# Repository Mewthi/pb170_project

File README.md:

LED - LA,LB,LC,LD,LE
Vstupy generovane citacom - (0-3)

    I       Q0    Q1    Q2    Q3    Q4
    00 -> ( 16 ->  8 ->  4 ->  2 ->  1)  
    01 -> ( 16 ->  1 ->  8 ->  2 ->  4) 
    10 -> ( 17 -> 10 ->  4 -> 20 -> 21)  
    11 -> (  4 -> 10 -> 17 -> 10 ->  4)  
  
Podrobna dokumentacia v /tex/main.pdf

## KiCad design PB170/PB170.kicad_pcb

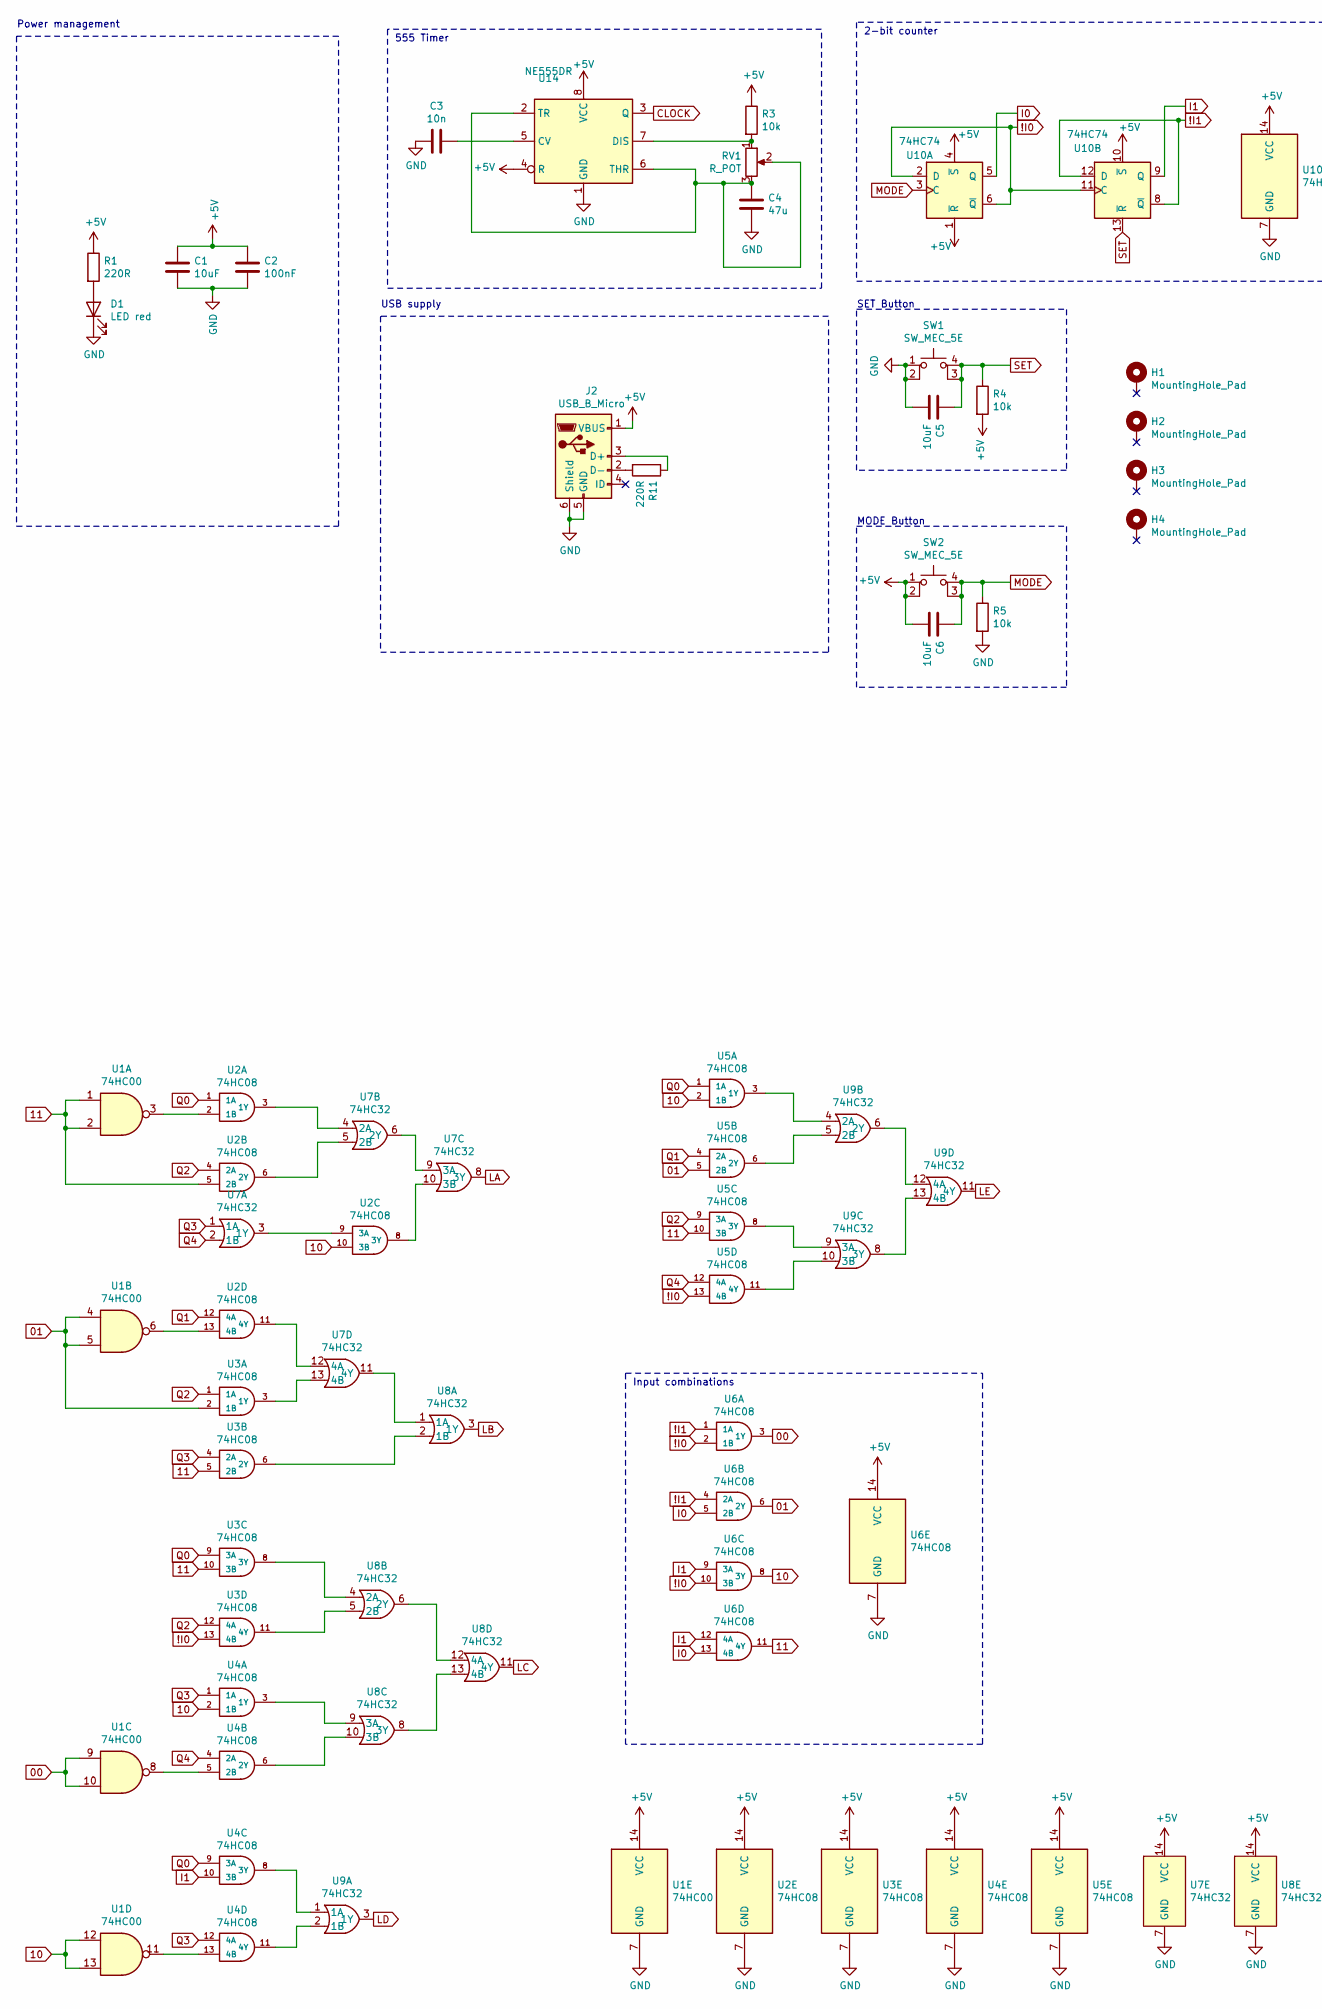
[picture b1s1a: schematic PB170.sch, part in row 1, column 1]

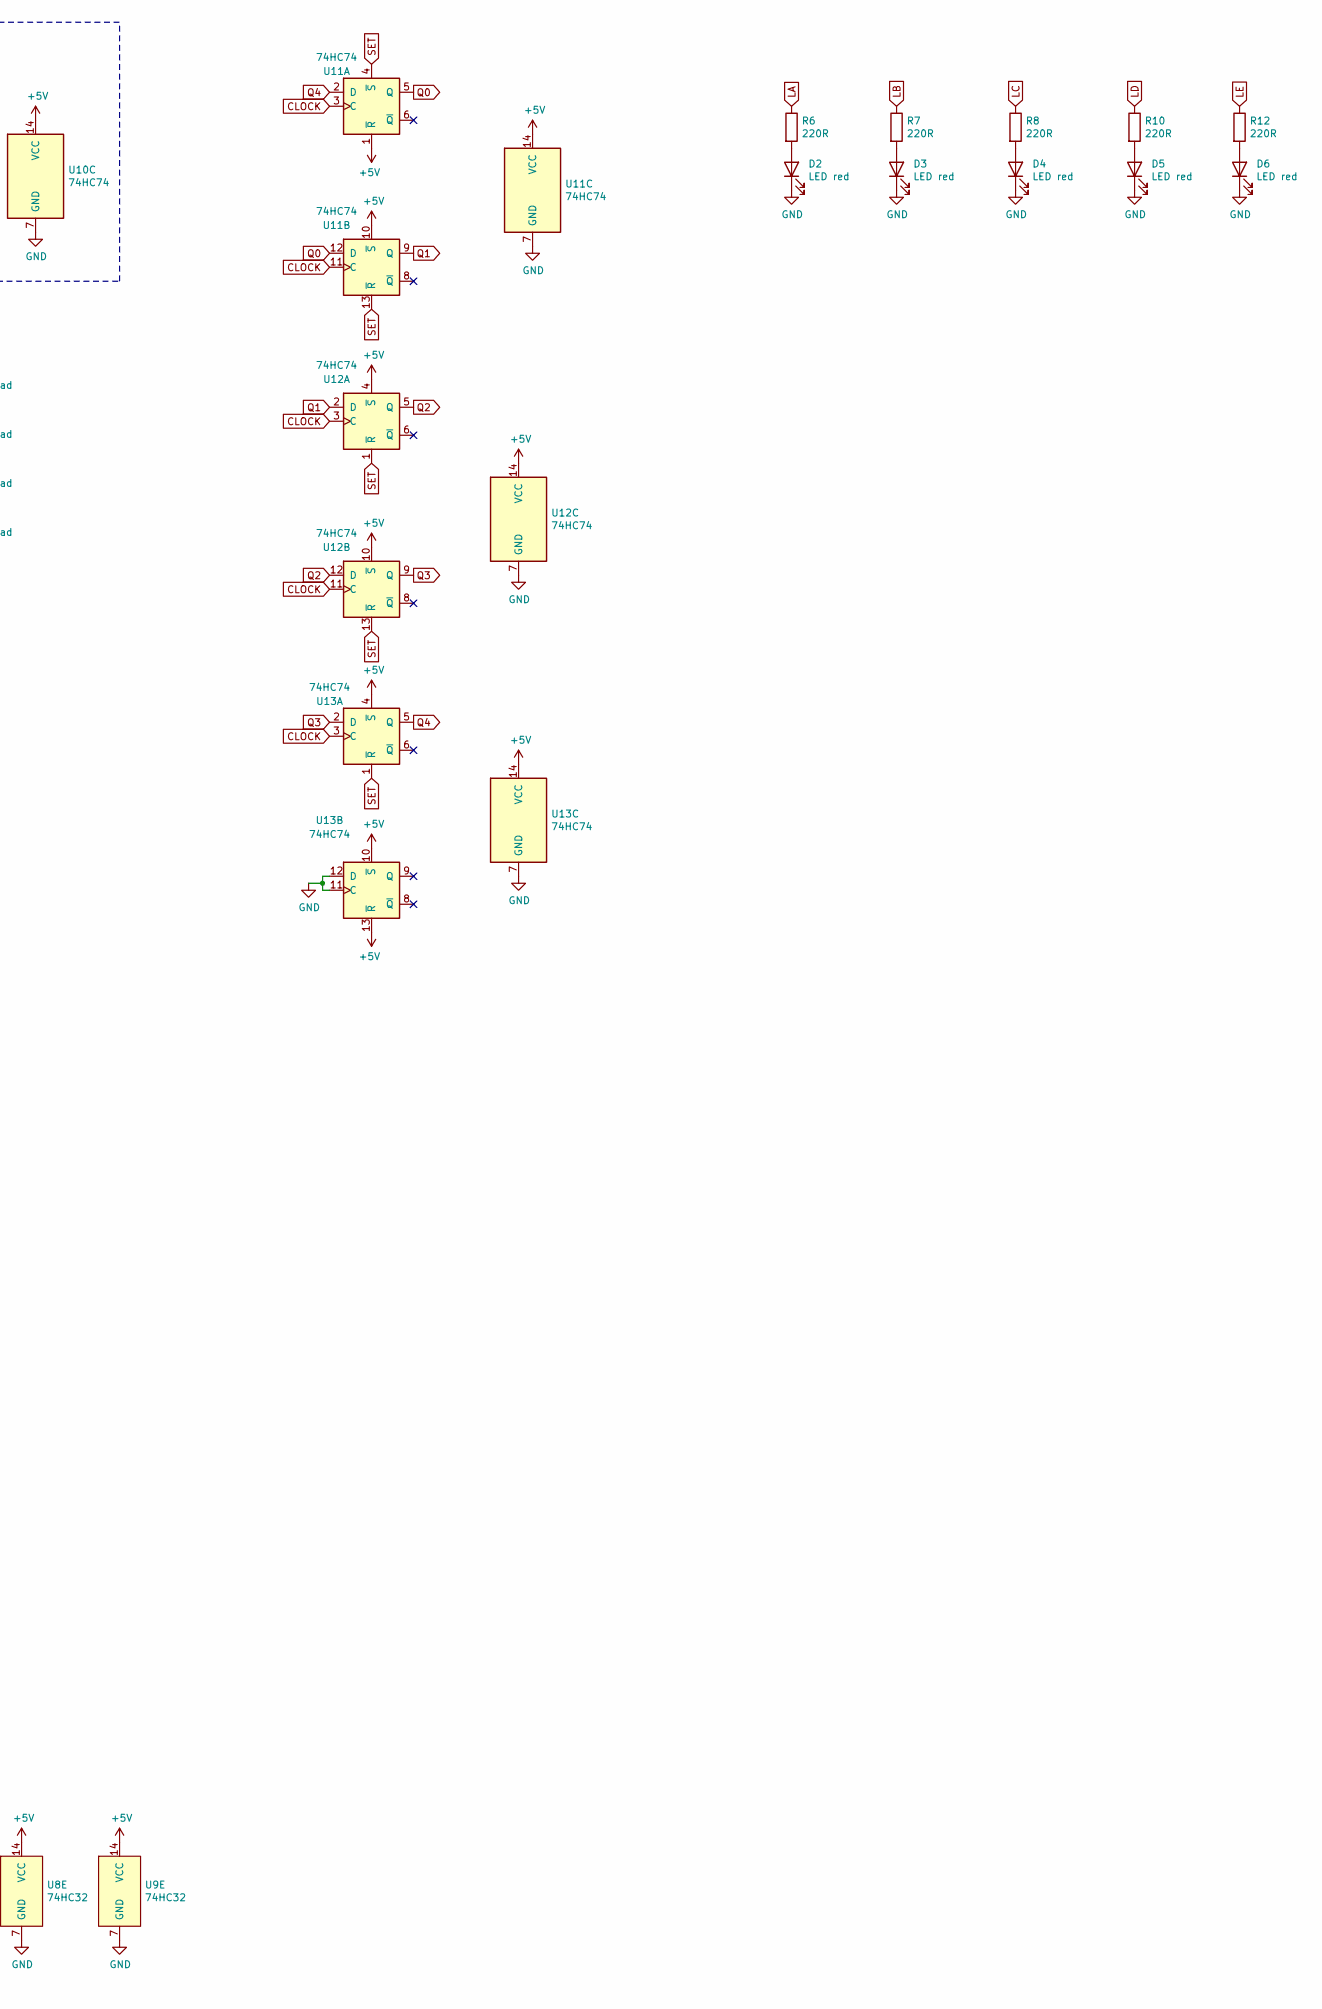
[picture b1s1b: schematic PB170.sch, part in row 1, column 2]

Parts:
C1, C5, C6: 10uF; C0805; LCSC C15850
C2: 100nF; C0603; LCSC C14663
C3: 10n; C0402; LCSC C15195
C4: 47u; C0805; LCSC C45783
D1, D2, D3, D4, D5, D6: LED red; LED0603-R-RD; LCSC C2286
H1, H2, H3, H4: MountingHole_Pad; MountingHole_3.2mm_M3_Pad
J2: USB_B_Micro; MICRO-USB-SMD_MICROXNJ; LCSC C404969
R1, R6, R7, R8, R10, R11, R12: 220R; R0603; LCSC C22962
R3, R4, R5: 10k; R0603; LCSC C25804
RV1: R_POT; potentiometer10k; LCSC C132879
SW1, SW2: SW_MEC_5E; TactileSwitch_C381064; LCSC C381064
U1: 74HC00; TSSOP-14_L5.0-W4.4-P0.65-LS6.4-BL; LCSC C6807
U2, U3, U4, U5, U6: 74HC08; SOIC-14_L8.7-W3.9-P1.27-LS6.0-BL; LCSC C5593
U7, U8, U9: 74HC32; SOIC-14_L8.7-W3.9-P1.27-LS6.0-BL; LCSC C5632
U10, U11, U12, U13: 74HC74; TSSOP-14_L5.0-W4.4-P0.65-LS6.4-BL; LCSC C6761
U14: NE555DR; SOIC-8_L4.9-W3.9-P1.27-LS6.0-BL; LCSC C7593

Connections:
00: U1.9, U1.10, U6.3 (1Y)
01: U1.4, U1.5, U3.2 (1B), U5.5 (2B), U6.6 (2Y)
10: U1.12, U1.13, U2.10 (3B), U4.2 (1B), U5.2 (1B), U6.8 (3Y)
11: U1.1, U1.2, U2.5 (2B), U3.5 (2B), U3.10 (3B), U5.10 (3B), U6.11 (4Y)
!I0: U3.13 (4B), U5.13 (4B), U6.2 (1B), U6.10 (3B), U10.2 (D), U10.6 (~Q), U10.11 (C)
!I1: U6.1 (1A), U6.4 (2A), U10.8 (~Q), U10.12 (D)
+5V: C1.1, C2.1, C6.2, J2.1 (VBUS), R1.1, R3.1, R4.2, SW2.1, SW2.2, U1.14 (VCC), U2.14 (VCC), U3.14 (VCC), U4.14 (VCC), U5.14 (VCC), U6.14 (VCC), U7.14 (VCC), U8.14 (VCC), U9.14 (VCC), U10.1 (~R), U10.4 (~S), U10.10 (~S), U10.14 (VCC), U11.1 (~R), U11.10 (~S), U11.14 (VCC), U12.4 (~S), U12.10 (~S), U12.14 (VCC), U13.4 (~S), U13.10 (~S), U13.13 (~R), U13.14 (VCC), U14.4 (R), U14.8 (VCC); also elsewhere on the board
CLOCK: U11.3 (C), U11.11 (C), U12.3 (C), U12.11 (C), U13.3 (C), U14.3 (Q)
GND: C1.2, C2.2, C3.2, C4.2, C5.2, D1.1 (K), D2.1 (K), D3.1 (K), D4.1 (K), D5.1 (K), D6.1 (K), J2.5 (GND), J2.6 (Shield), R5.2, SW1.1, SW1.2, U1.7 (GND), U2.7 (GND), U3.7 (GND), U4.7 (GND), U5.7 (GND), U6.7 (GND), U7.7 (GND), U8.7 (GND), U9.7 (GND), U10.7 (GND), U11.7 (GND), U12.7 (GND), U13.7 (GND), U13.11 (C), U13.12 (D), U14.1 (GND)
I0: U6.5 (2B), U6.13 (4B), U10.5 (Q)
I1: U4.10 (3B), U6.9 (3A), U6.12 (4A), U10.9 (Q)
LA: R6.1, U7.8 (3Y)
LB: R7.1, U8.3 (1Y)
LC: R8.1, U8.11 (4Y)
LD: R10.1, U9.3 (1Y)
LE: R12.1, U9.11 (4Y)
MODE: C6.1, R5.1, SW2.3 (K), SW2.4 (A), U10.3 (C)
unnamed: C3.1, U14.5 (CV)
unnamed: C4.1, RV1.2, RV1.3, U14.2 (TR), U14.6 (THR)
unnamed: D1.2 (A), R1.2
unnamed: D2.2 (A), R6.2
unnamed: D3.2 (A), R7.2
unnamed: D4.2 (A), R8.2
unnamed: D5.2 (A), R10.2
unnamed: D6.2 (A), R12.2
unnamed: J2.2 (D-), R11.2
unnamed: J2.3 (D+), R11.1
unnamed: R3.2, RV1.1, U14.7 (DIS)
unnamed: U1.3, U2.2 (1B)
unnamed: U1.6, U2.13 (4B)
unnamed: U1.8, U4.5 (2B)
unnamed: U1.11, U4.13 (4B)
unnamed: U2.3 (1Y), U7.4 (2A)
unnamed: U2.6 (2Y), U7.5 (2B)
unnamed: U2.8 (3Y), U7.10 (3B)
unnamed: U2.9 (3A), U7.3 (1Y)
unnamed: U2.11 (4Y), U7.12 (4A)
unnamed: U3.3 (1Y), U7.13 (4B)
unnamed: U3.6 (2Y), U8.2 (1B)
unnamed: U3.8 (3Y), U8.4 (2A)
unnamed: U3.11 (4Y), U8.5 (2B)
unnamed: U4.3 (1Y), U8.9 (3A)
unnamed: U4.6 (2Y), U8.10 (3B)
unnamed: U4.8 (3Y), U9.1 (1A)
unnamed: U4.11 (4Y), U9.2 (1B)
unnamed: U5.3 (1Y), U9.4 (2A)
unnamed: U5.6 (2Y), U9.5 (2B)
unnamed: U5.8 (3Y), U9.9 (3A)
unnamed: U5.11 (4Y), U9.10 (3B)
unnamed: U7.6 (2Y), U7.9 (3A)
unnamed: U7.11 (4Y), U8.1 (1A)
unnamed: U8.6 (2Y), U8.12 (4A)
unnamed: U8.8 (3Y), U8.13 (4B)
unnamed: U9.6 (2Y), U9.12 (4A)
unnamed: U9.8 (3Y), U9.13 (4B)
Q0: U2.1 (1A), U3.9 (3A), U4.9 (3A), U5.1 (1A), U11.5 (Q), U11.12 (D)
Q1: U2.12 (4A), U5.4 (2A), U11.9 (Q), U12.2 (D)
Q2: U2.4 (2A), U3.1 (1A), U3.12 (4A), U5.9 (3A), U12.5 (Q), U12.12 (D)
Q3: U3.4 (2A), U4.1 (1A), U4.12 (4A), U7.1 (1A), U12.9 (Q), U13.2 (D)
Q4: U4.4 (2A), U5.12 (4A), U7.2 (1B), U11.2 (D), U13.5 (Q)
SET: C5.1, R4.1, SW1.3 (K), SW1.4 (A), U10.13 (~R), U11.4 (~S), U11.13 (~R), U12.1 (~R), U12.13 (~R), U13.1 (~R)

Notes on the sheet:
USB supply
Power management
555 Timer
SET Button
2-bit counter
Input combinations
MODE Button

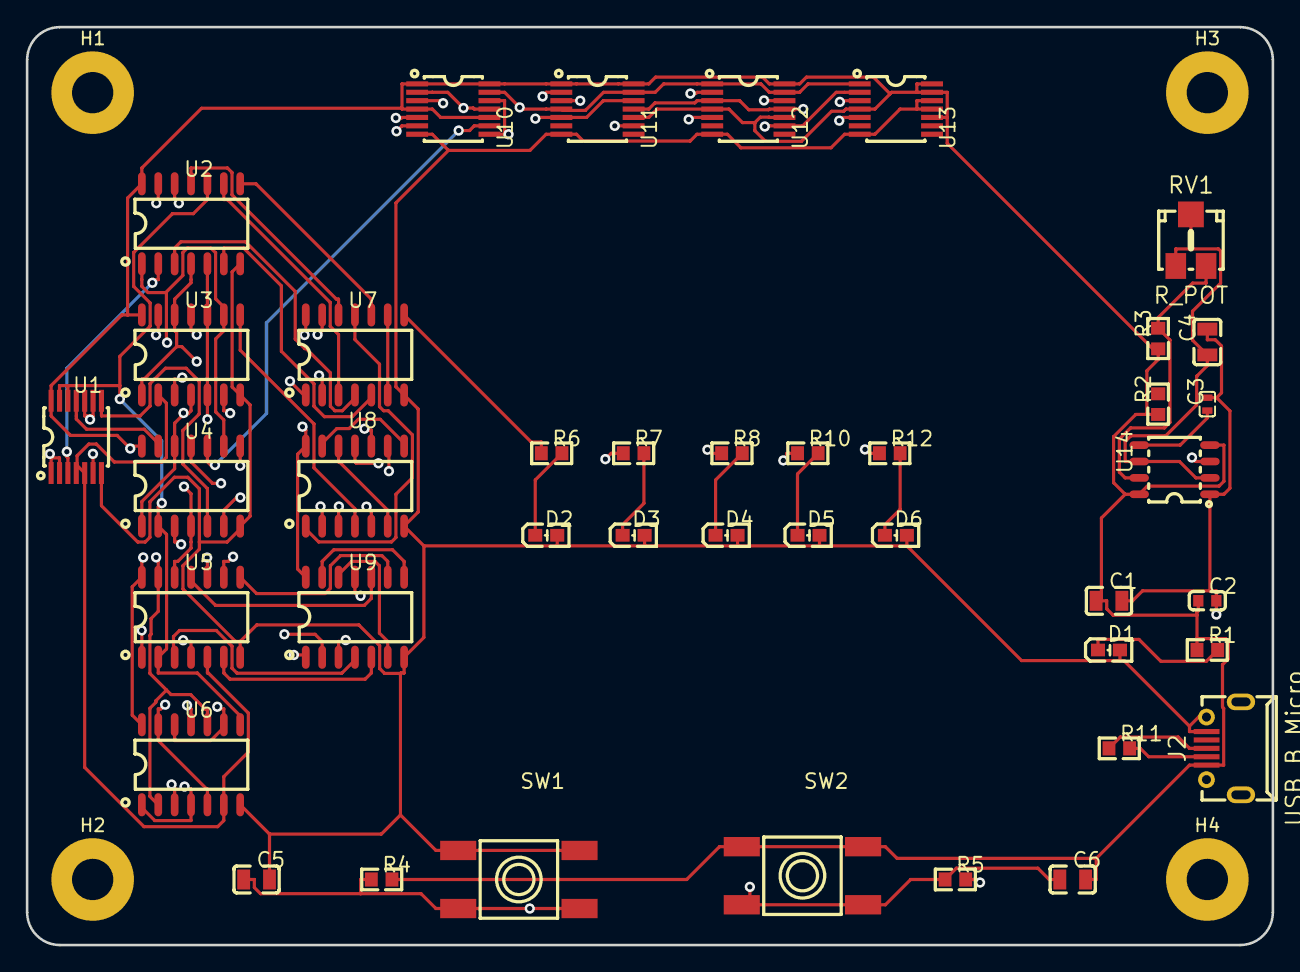
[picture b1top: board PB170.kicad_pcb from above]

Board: 4 copper layers, 96.5 x 71.1 mm, 45 parts (0 on the bottom side), 61 nets.

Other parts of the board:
R2: 10k; R0603

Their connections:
+5V: R2.1; also elsewhere on the board

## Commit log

2021-02-09 first commit. hello world
2021-02-09 I somehow documented this, WIP though
2021-02-09 title changed
2021-02-10 10-02-Martin
2021-02-10 Flip-Flops changed
2021-02-11 11-02-2021 Martin
2021-02-11 added new parts
2021-02-11 KiCad crashing fixup, probably
2021-02-11 11-02-2021 02 Martin
2021-02-11 PB170.sch change
2021-02-11 11-02-2021 03 Martin
2021-02-11 LA changed
2021-02-11 added some labels
2021-02-11 removed LBsch.pro
2021-02-12 12-02-2021 Martin
2021-02-12 labels changed
2021-02-12 added LEDs, mby we could try to start routing
2021-02-12 okay done
2021-02-12 refs changed
2021-02-12 annotated, needs footprints exported
2021-02-12 need needs capacitor footprints
2021-02-13 Capacitors footprints added, gl & hf routing
2021-02-13 13-02-2021 Martin
2021-02-14 FreeRouting is a very useful java application
2021-02-14 14-02-2021 uzivatelskaPrirucka Martin
2021-02-17 grounded unused pins, added 3D models and photo
2021-02-17 17-02-2021 Martin prirucka
2021-02-17 17-02-2021 Martin potenciometer
2021-02-17 uzivatelskaPDF
2021-02-18 grammar mistakes in docs
2021-02-18 documentation improved
